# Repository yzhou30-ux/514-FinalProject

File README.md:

# FreshSense: Smart Food Tracking and Management System

📄 [View Final Presentation (PDF)](FreshsenseDeck.pdf)

This smart refrigerator labeling system integrates multiple individual sensor "tags" with an external magnetic display "hub." The tags automatically monitor and record the time and humidity of stored food items from the moment they are detached from the hub. This system offers a cost-effective solution for food management and improves storage tracking to reduce waste.

---

## TAG: Sensor

The TAG is a sensing device responsible for:
- Collecting environmental data (humidity, temperature, battery percentage, and time since detaching).
- Transmitting data to the HUB via BLE.
- Supporting contact charging for its battery.

### Components:
- **XIAO ESP32C**
- **HTU21D** (Sleep Humidity Sensor)
- **LIR2032 Coin Cell** (Rechargeable)

### What data does the TAG collect?
- Humidity & Temperature  
- Time since detaching  
- Battery Percentage  

---

## HUB: Display

The HUB is a display controller that:
- Receives data from the TAG.
- Displays information using motor-needle, LED, and OLED interfaces.
- Manages multiple TAG addresses and states.
- Switches active TAGs.
- Monitors and displays system battery percentage.

### Components:
- **XIAO ESP32C**  
- **28BYJ-48 Stepper Motor, Driver & Needle**  
- **LED**  
- **OLED Display** (128x64)  
- **Piezoelectric Button**  
- **7.4V 2S LiPo Battery**  
  - **TP5100**, **MP1584**, **LM2596**, **TP4056**

### What functions does the HUB serve?
- **Display**: Motor-needle and LED display.  
- **Other Interfaces**: OLED display, button.  
- **Contact Charging**: For sensors.  
- **Management**: Manage sensor addresses, detect if a TAG is present, and receive TAG data.  
- **Battery Monitoring**: Display system battery percentage.  

---

## System Communication Diagram
*(Based on BLE Communication)*

---

## System Workflow
*(Detailed workflow of TAG and HUB interactions)*

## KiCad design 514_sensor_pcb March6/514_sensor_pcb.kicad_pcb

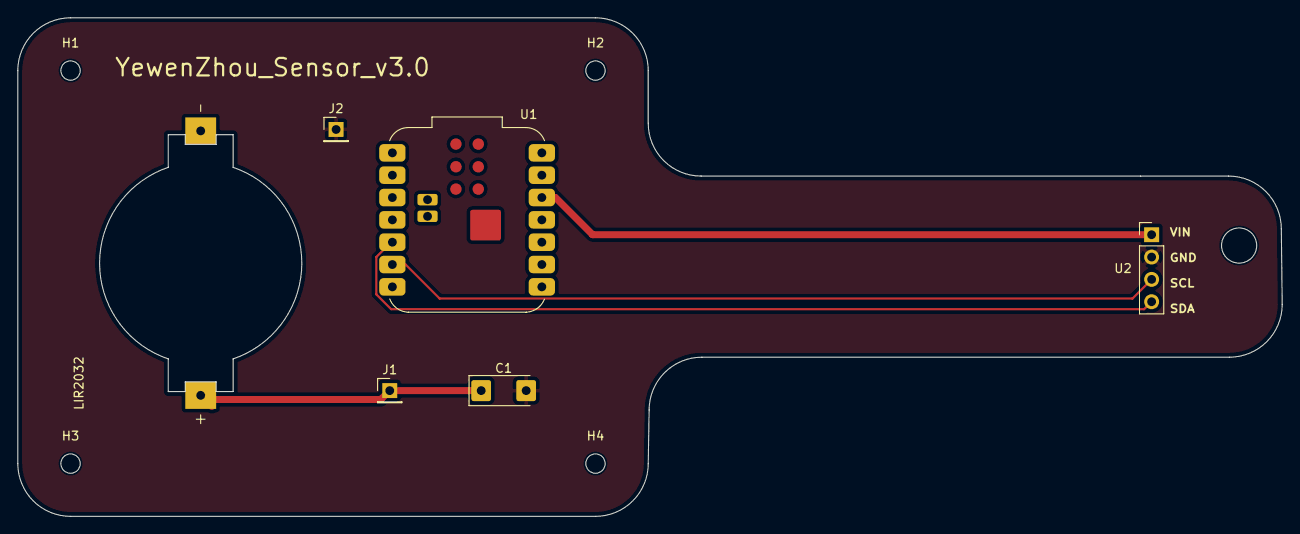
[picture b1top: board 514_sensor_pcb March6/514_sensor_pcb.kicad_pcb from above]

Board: 2 copper layers, 143.8 x 56.7 mm, 10 parts (0 on the bottom side), 5 nets.

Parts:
C1: C_Polarized_470uF; CP_EIA-6032-28_Kemet-C_HandSolder
H1, H2, H3, H4: MountingHole_2.2mm_M2
J1, J2: PinHeader_1x01_P2.54mm; PinHeader_1x01_P2.54mm_Vertical
LIR2032: Battery 3.7V; BAT_1057
U1: XIAO ESP32C3; MCU_Seeed_ESP32C3
U2: HTU21D breakoutboard; PinHeader_1x04_P2.54mm_Vertical

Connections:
GND: C1.2, J2.1, U1.13 (GND), U2.2
unnamed: U1.5 (D4), U2.4
unnamed: U1.6 (D5), U2.3
unnamed: U1.12 (VCC_3V3), U2.1
VCC: C1.1, J1.1

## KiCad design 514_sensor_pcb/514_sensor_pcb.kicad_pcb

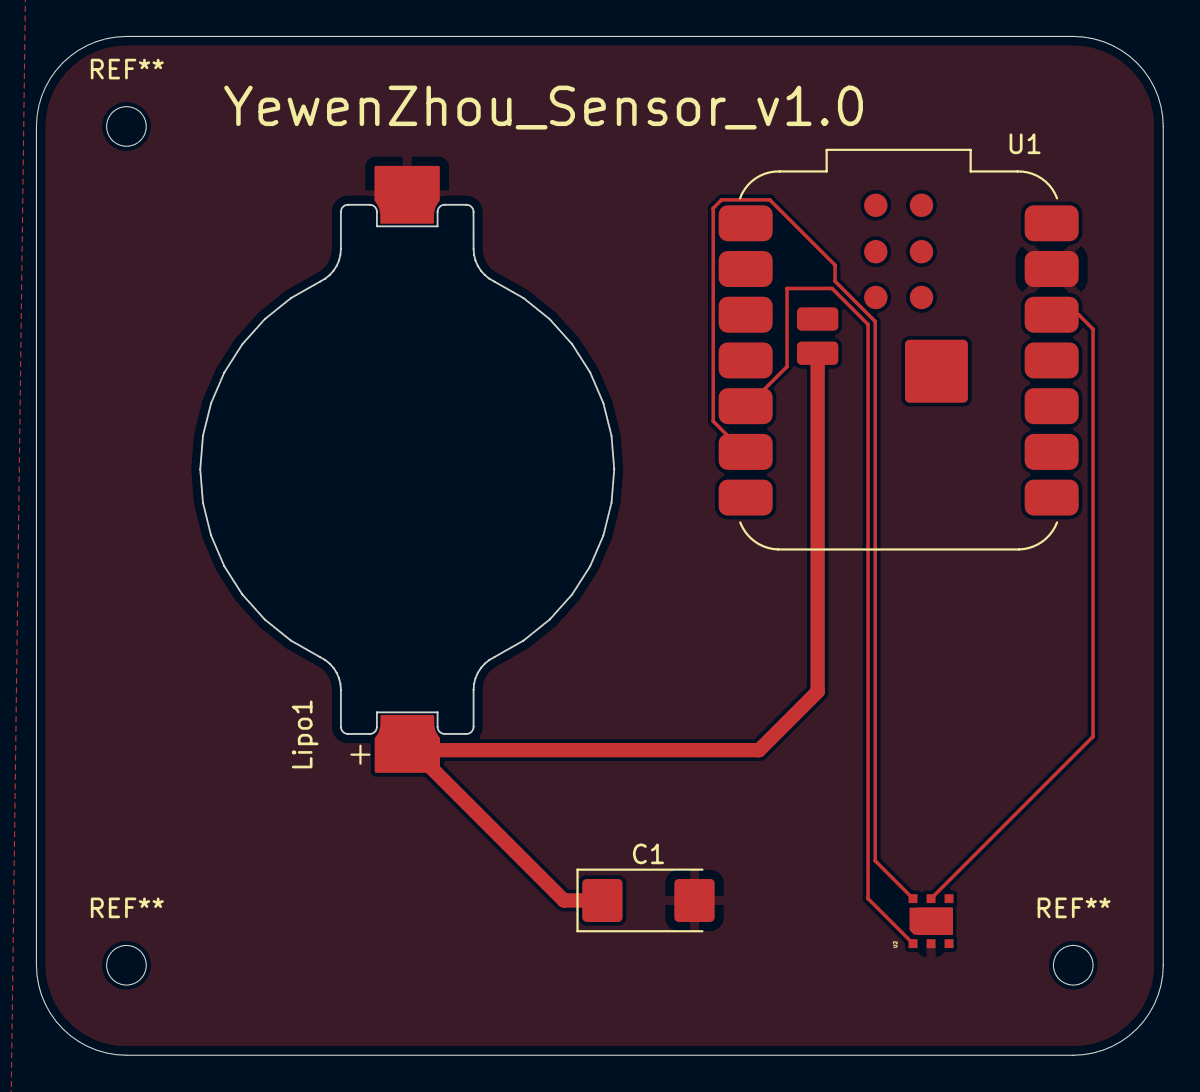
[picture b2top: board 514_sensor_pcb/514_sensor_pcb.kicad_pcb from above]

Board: 2 copper layers, 62.6 x 56.6 mm, 4 parts (0 on the bottom side), 5 nets.

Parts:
C1: C_Polarized_US; CP_EIA-6032-28_Kemet-C_HandSolder
Lipo1: Battery; BatteryHolder_Keystone_1057_1x2032
U1: XIAO ESP32C3; MCU_Seeed_ESP32C3
U2: HTU21D; QFN100P300X300X100-7N

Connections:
GND: C1.2, Lipo1.2 (-), U1.13 (GND), U2.2 (GND)
unnamed: U1.5 (D4), U2.1 (SDA)
unnamed: U1.6 (D5), U2.6 (SCL)
unnamed: U1.12 (VCC_3V3), U2.5 (VDD)
VCC: C1.1, Lipo1.1 (+)

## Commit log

2026-01-20 Initial commit: 514 Final Project
2026-01-20 Fix image link with URL encoding for spaces
2026-01-20 Fix all image links with URL encoding for spaces
2026-01-26 Update PCB sensor library files - Add HTU210D symbol, New_Library backup and symbol files
2026-02-07 Initial commit from workspace
2026-03-02 Update project files - Add 514_code, sensor/display PCB updates, enclosure folder, and additional resources
2026-03-19 Update project files
